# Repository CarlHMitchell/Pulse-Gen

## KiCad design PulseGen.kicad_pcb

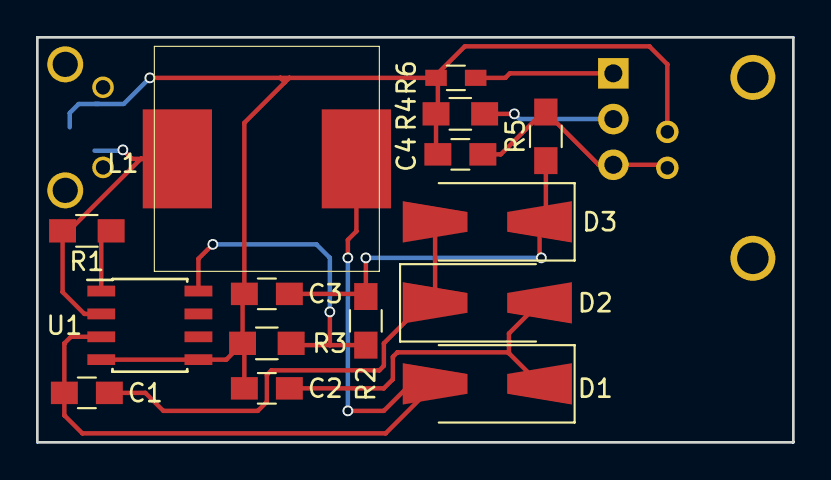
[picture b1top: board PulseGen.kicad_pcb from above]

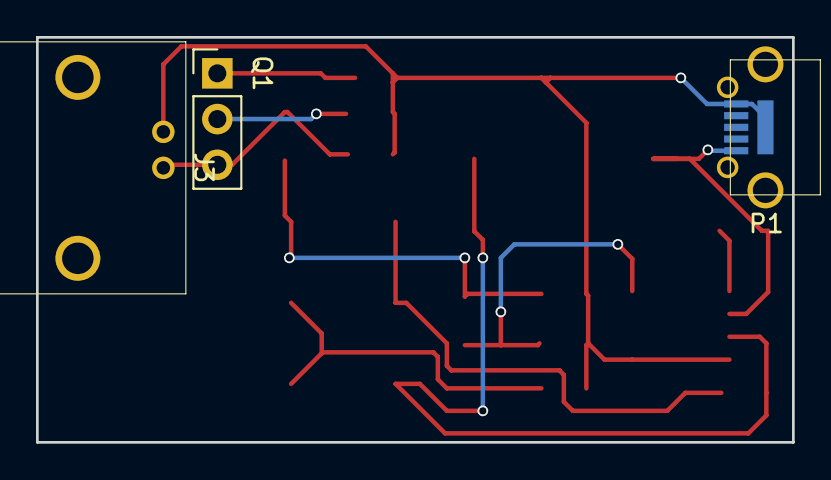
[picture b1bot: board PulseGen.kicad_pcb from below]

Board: 2 copper layers, 42.0 x 22.5 mm, 18 parts (3 on the bottom side), 11 nets.

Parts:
C1, C2, C3: 470n; C_0805_HandSoldering
C4: 2p; C_0805_HandSoldering
D1, D2, D3: RS1M; D_SMA-SMB_Universal_Handsoldering
J3: CONN_COAXIAL; BNC_Right_angle
L1: 150u; Eaton_DR_125
P1: USB_OTG; USB_Micro-B_UJ2-MIBH2-4-SMT_CircMounts
Q1: 2N2369A; Socket_Strip_Straight_1x03_Pitch2.54mm
R1: 220R; R_0805_HandSoldering
R2: 10M; R_0805_HandSoldering
R3: 24k; R_0805_HandSoldering
R4: 10k; R_0805_HandSoldering
R5: 1M; R_0805_HandSoldering
R6: 50R; R_0603_HandSoldering
U1: LT1073; SOIC-8_3.9x4.9mm_Pitch1.27mm

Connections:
+5V: L1.2, P1.1, R1.2, U1.2
GND: C2.2, C3.2, C4.1, J3.2, P1.5, P1.6, R3.2, R4.2, R6.2, U1.4, U1.5
unnamed: C1.1, D2.1, D3.2
unnamed: C1.2, D1.2, L1.1, U1.3
unnamed: C2.1, D1.1, D2.2
unnamed: C3.1, D3.1, R2.1, R5.1
unnamed: C4.2, J3.1, Q1.3, R5.2
unnamed: Q1.1, R6.1
unnamed: Q1.2, R4.1
unnamed: R1.1, U1.1
unnamed: R2.2, R3.1, U1.8

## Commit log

2017-12-22 Initial commit
    PCB in KiCAD, simulation in LTSPICE.
